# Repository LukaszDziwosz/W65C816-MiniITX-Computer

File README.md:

# W65C816 Modern Computer

A two-board, retro-inspired computer built around a physical WDC W65C816S CPU. The CPU is the computer: it runs the boot firmware, operating system, applications, game logic, and interrupt handlers. An RP2354B daughterboard acts as a memory-mapped multimedia and I/O chipset.

Revision A deliberately combines socketed, through-hole 65xx-style hardware with modern coprocessor-based video, audio, storage, USB, and networking.

## Revision-A architecture

| Area | Decision |
| --- | --- |
| Main processor | W65C816S6PG-14, DIP-40, 5 V |
| Main clock | 8 MHz supported target; 1 MHz and 4 MHz bring-up |
| Main RAM | Four fitted AS6C4008-55PIN DIP-32 SRAMs (2 MiB) |
| RAM expansion | Four optional AS6C4008 footprints, for 4 MiB maximum |
| Boot Flash | SST39SF040-55-4I-NHE in a PLCC-32 socket |
| Mainboard glue | 5 V 74AHC, preferably socketed DIP parts |
| Daughterboard | RP2354B at 3.3 V with QMI PSRAM |
| Networking | ESP32-C3, sole controller of the W5500 Ethernet device |
| Mainboard/daughterboard connector | 98-pin ISA-form-factor, project-specific signalling |

The ISA-style connector is a mechanical choice only. It does **not** implement the ISA electrical or protocol standard.

## System model

```text
5 V system input
├── W65C816 mainboard: CPU, SRAM, Flash, AHC glue, wait-state logic
└── 3.3 V regulator
    └── RP2354B daughterboard: PSRAM, video, audio, USB, SD, ESP32-C3

W65C816 ── memory-mapped registers/FIFOs ── RP2354B ── UART ── ESP32-C3 ── W5500
```

The RP2354B is a chipset, not a transparent MMU or replacement CPU. Its PSRAM is used for media buffers, assets, DMA, blitter operations, and staging. Revision A does not execute W65C816 code from RP PSRAM.

## CPU/RP interface

The RP is selected over `$F00000-$F1FFFF`; its 1 KiB interface is deliberately mirrored because only A0-A9 are interpreted.

| Range | Function |
| --- | --- |
| `$F00000-$F000FF` | Control and status registers |
| `$F00100-$F001FF` | Command FIFO write window |
| `$F00200-$F002FF` | Response FIFO read window |
| `$F00300-$F003FF` | Input/event FIFO read window |

The first wait state for an RP access is generated in deterministic mainboard hardware. RP PIO handles the bus-cycle handshake; RP firmware handles commands and asynchronous work. Slow operations such as SD, network, DMA, and blits must complete asynchronously and report completion through the RP interrupt controller.

## Safety and timing principles

- SRAM is intended to be zero-wait at 8 MHz, with at least 10 ns calculated worst-case margin.
- Flash starts with one hardware wait state. Zero-wait Flash is optional only after calculation and logic-analyser verification.
- U2 is a 74AHC573 transparent bank latch, controlled by a single 74AHC04 inversion of PHI2.
- U3 remains a 74AHC245 memory-side data transceiver unless timing and loading analysis proves a better arrangement.
- U16 is an SN74LXC8T245 dual-supply transceiver with A/VCCA on the 5 V system data bus and
  B/VCCB on the 3.3 V RP data bus. With the device's convention, `DIR = NOT(RWB)`: CPU write
  (`RWB=0`) is A-to-B and CPU read (`RWB=1`) is B-to-A.
- RDY and IRQ are 5 V pulled-up, open-drain signals; the daughterboard never drives either high.
- The mainboard must boot without the daughterboard, with the RP held in reset, and with no RP firmware.
- Every IC requires local 100 nF decoupling.

The RP boundary is intentionally conservative. Every 5 V connector input uses a dedicated
3.3 V input buffer at the daughterboard boundary; a direct 5 V RP GPIO connection is not the
normal level-shifting method. An individually verified RP2354B FT GPIO may be used directly only
as a documented input-only fault-resilience fallback, only while IOVDD is at 3.3 V, and never
on an analog-capable or other non-FT pin.

**IOVDD is operating at 3.3 V !!!!!** Direct 5 V must never reach an unpowered or disabled
3.3 V domain. **Non-FT pins must not receive 5 V. FT pins should receive 3.3 V by design;
5 V tolerance is only a fault-resilience constraint. !!!**

## Bring-up progression

1. Mainboard only at 1 MHz, then 4 MHz and 8 MHz.
2. Verify Flash wait-state, SRAM, bank-latch, decode, and write-strobe timing.
3. Fit a passive/reset-held daughterboard and verify no contention or phantom powering.
4. Bring up RP registers, FIFO, interrupts, PSRAM/DMA, ESP networking, then SD/USB/video/audio.
5. Consider 10 MHz, 12 MHz, and 14 MHz only after full timing captures and stress testing at 8 MHz.

## Repository layout

```text
Mainboard/                 KiCad 10 mainboard project
RP2350-Daughterboard/      KiCad 10 daughterboard project (name retained for compatibility)
Shared-Libraries/          Shared symbols and footprints
Documentation/             Project documentation
Firmware/                  CPU, RP, and ESP firmware
board_design.txt           Detailed Revision-A electrical/design contract
AGENTS.md                  Mandatory design and KiCad workflow rules
```

See [board_design.txt](board_design.txt) for the complete architecture, timing, interface, implementation, and validation contract.

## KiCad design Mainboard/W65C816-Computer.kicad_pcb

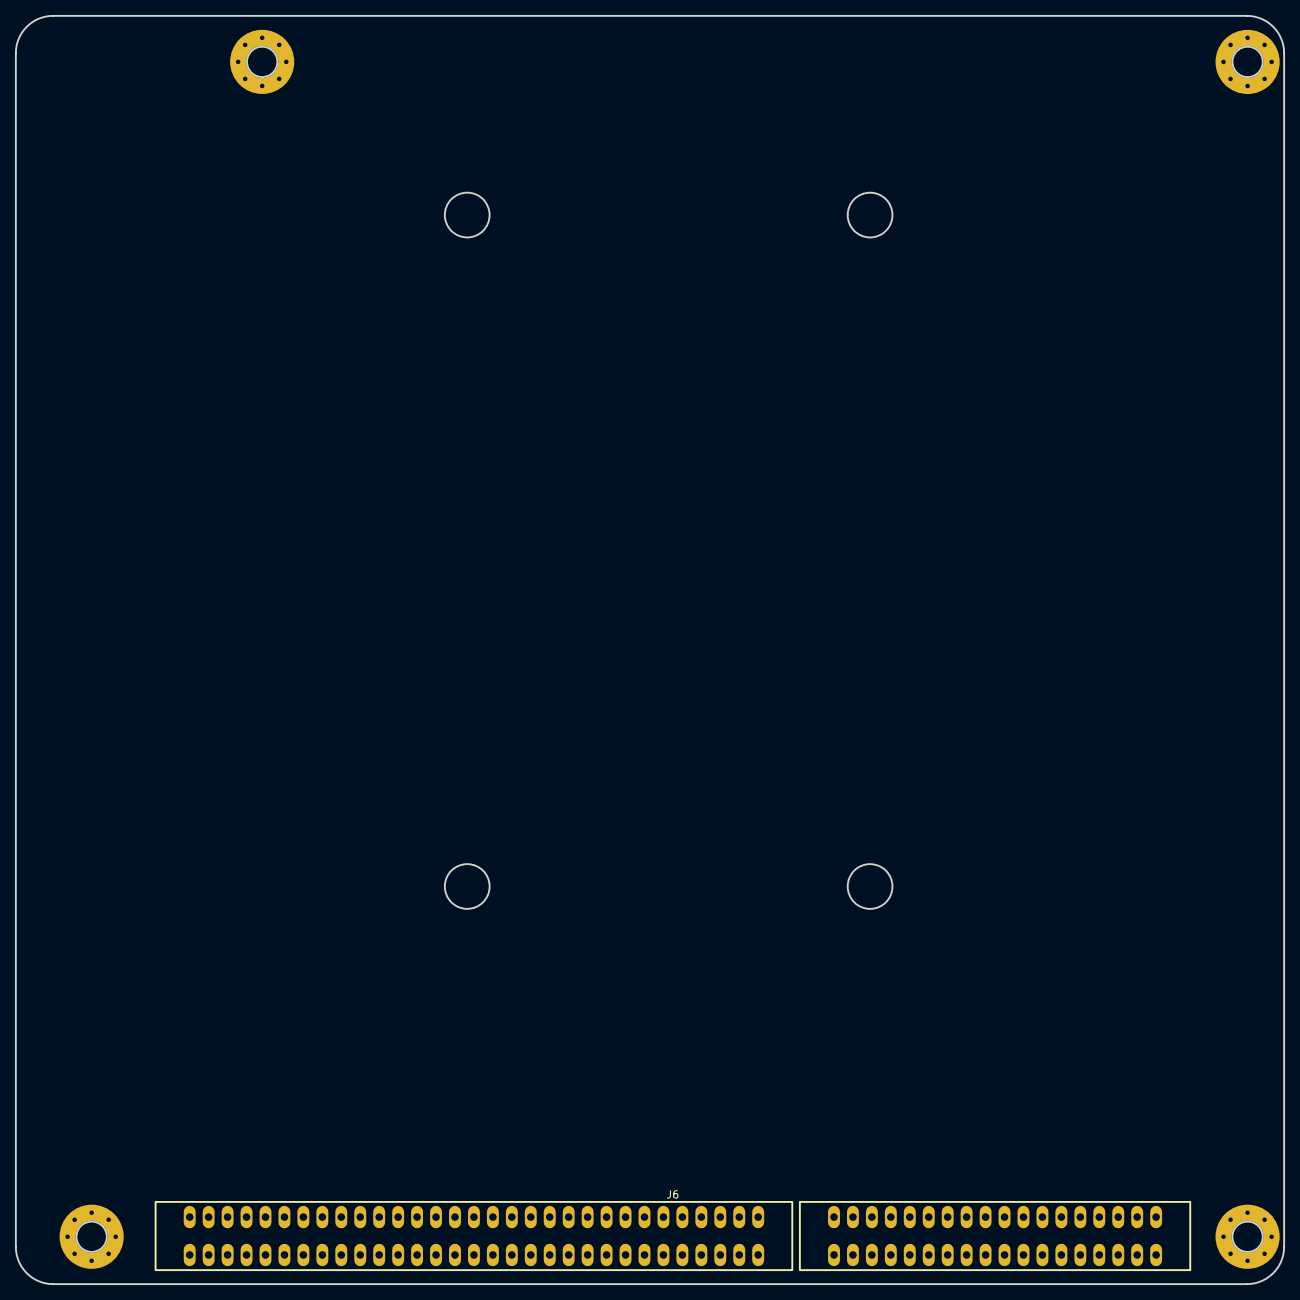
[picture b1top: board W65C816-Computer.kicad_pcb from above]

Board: 2 copper layers, 170.0 x 170.0 mm, 5 parts (0 on the bottom side), 3 nets, no tracks yet.

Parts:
H1, H2, H3, H4: MountingHole; MountingHole_4.3mm_M4_Pad_Via
J6: ISA16_DAUGHTER_BUS; ISA16_Slot

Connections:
+3V3: J6.2, J6.20, J6.42, J6.78
/+5V: J6.38, J6.40
GND: J6.1, J6.19, J6.37, J6.39, J6.41, J6.77, J6.80
